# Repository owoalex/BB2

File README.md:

# BB2
Open source BLDC motor controller supporting >100A @ 20-60v

BB2 © 2023 is licensed under Attribution-ShareAlike 4.0 International. To view a copy of this license, visit http://creativecommons.org/licenses/by-sa/4.0/

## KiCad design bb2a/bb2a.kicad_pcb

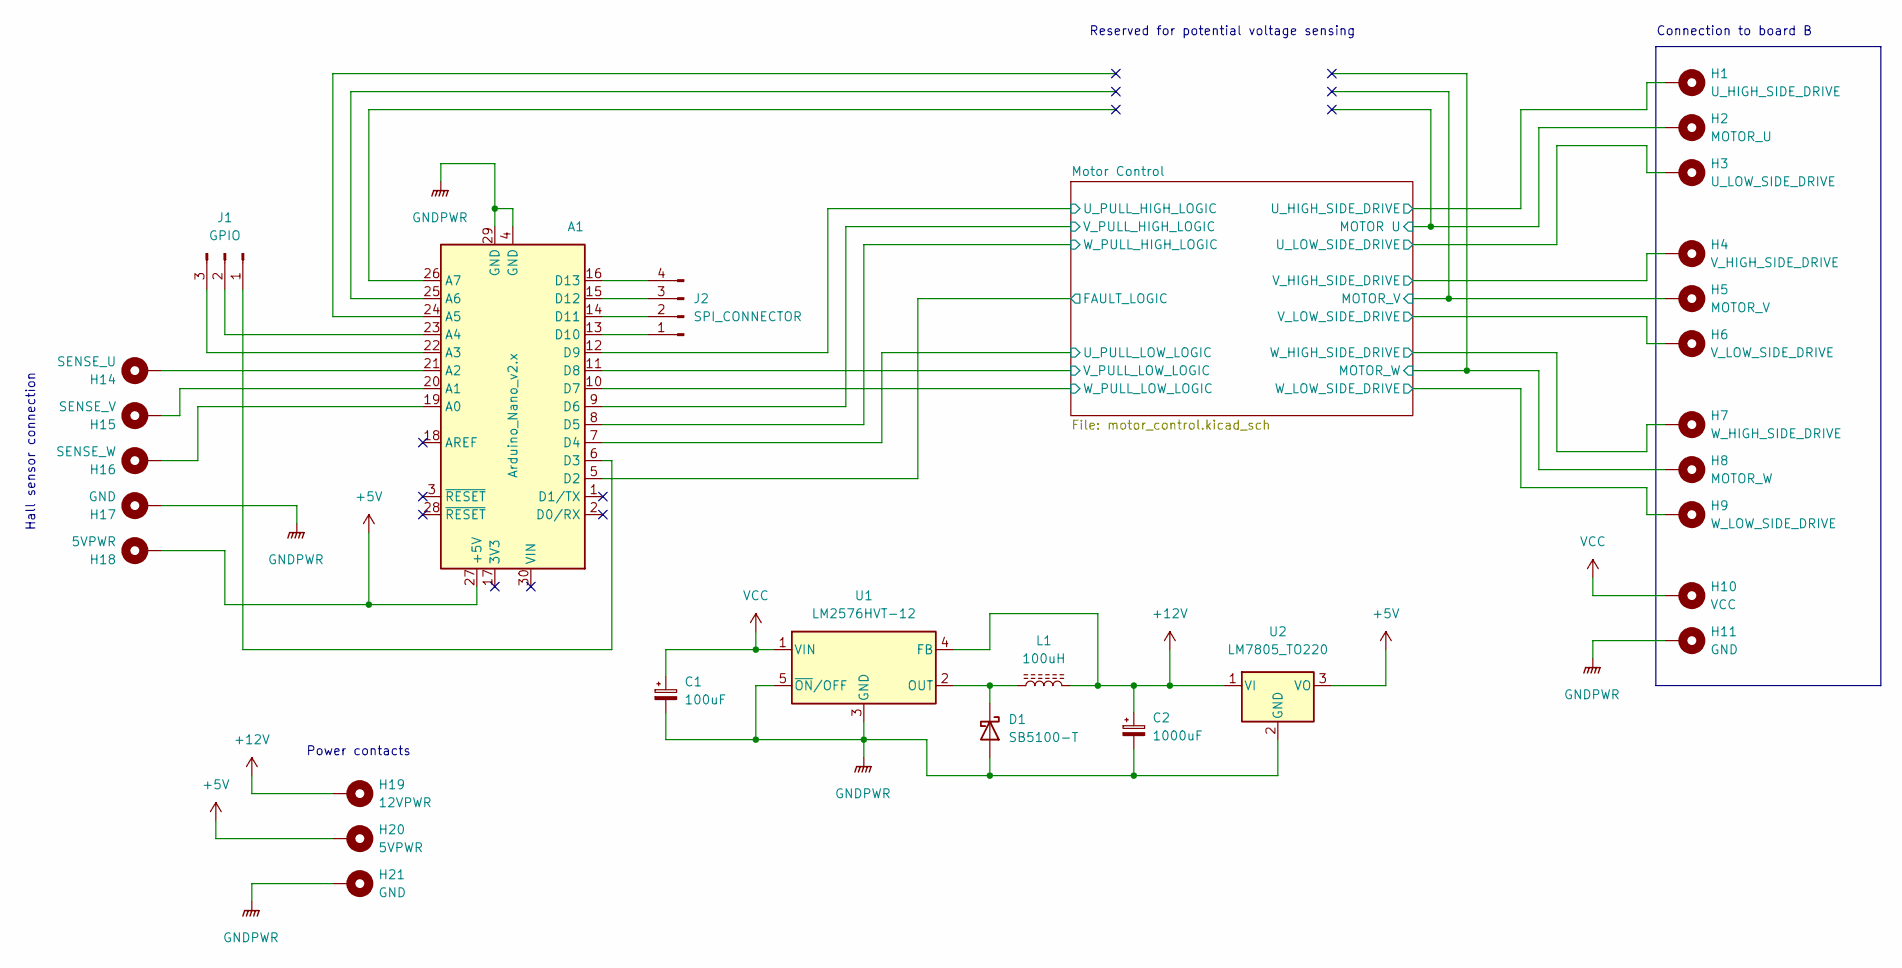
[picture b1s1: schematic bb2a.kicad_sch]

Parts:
A1: Arduino_Nano_v2.x; Arduino_Nano
C1: 100uF; CP_Radial_D6.3mm_P2.50mm
C2: 1000uF; CP_L18.0mm_D10.0mm_P5.00mm_Horizontal
D1: SB5100-T; D_DO-201AD_P15.24mm_Horizontal
H1: U_HIGH_SIDE_DRIVE; MountingHole_2.2mm_M2_Pad_Via
H2: MOTOR_U; MountingHole_2.2mm_M2_Pad_Via
H3: U_LOW_SIDE_DRIVE; MountingHole_2.2mm_M2_Pad_Via
H4: V_HIGH_SIDE_DRIVE; MountingHole_2.2mm_M2_Pad_Via
H5: MOTOR_V; MountingHole_2.2mm_M2_Pad_Via
H6: V_LOW_SIDE_DRIVE; MountingHole_2.2mm_M2_Pad_Via
H7: W_HIGH_SIDE_DRIVE; MountingHole_2.2mm_M2_Pad_Via
H8: MOTOR_W; MountingHole_2.2mm_M2_Pad_Via
H9: W_LOW_SIDE_DRIVE; MountingHole_2.2mm_M2_Pad_Via
H10: VCC; MountingHole_2.2mm_M2_Pad_Via
H11, H17, H21: GND; MountingHole_2.2mm_M2_Pad_Via
H14: SENSE_U; MountingHole_2.2mm_M2_Pad_Via
H15: SENSE_V; MountingHole_2.2mm_M2_Pad_Via
H16: SENSE_W; MountingHole_2.2mm_M2_Pad_Via
H18, H20: 5VPWR; MountingHole_2.2mm_M2_Pad_Via
H19: 12VPWR; MountingHole_2.2mm_M2_Pad_Via
J1: GPIO; PinHeader_1x03_P2.54mm_Vertical
J2: SPI_CONNECTOR; PinHeader_1x04_P2.54mm_Vertical
L1: 100uH; THT Toroidal Inductor Horizontal 25x12mm
U1: LM2576HVT-12; TO-220-5_P3.4x3.8mm_StaggerEven_Lead7.13mm_TabDown
U2: LM7805_TO220; TO-220-3_Horizontal_TabDown

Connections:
+5V: A1.27 (+5V), H18.1, H20.1, U2.3 (VO)
+12V: C2.1, H19.1, L1.2, U1.4 (FB), U2.1 (VI); also elsewhere on the board
/Motor Control/FAULT_LOGIC: A1.5 (D2); also elsewhere on the board
/Motor Control/MOTOR U: H2.1; also elsewhere on the board
/Motor Control/MOTOR_V: H5.1; also elsewhere on the board
/Motor Control/MOTOR_W: H8.1; also elsewhere on the board
/Motor Control/U_HIGH_SIDE_DRIVE: H1.1; also elsewhere on the board
/Motor Control/U_LOW_SIDE_DRIVE: H3.1; also elsewhere on the board
/Motor Control/U_PULL_HIGH_LOGIC: A1.12 (D9); also elsewhere on the board
/Motor Control/U_PULL_LOW_LOGIC: A1.7 (D4); also elsewhere on the board
/Motor Control/V_HIGH_SIDE_DRIVE: H4.1; also elsewhere on the board
/Motor Control/V_LOW_SIDE_DRIVE: H6.1; also elsewhere on the board
/Motor Control/V_PULL_HIGH_LOGIC: A1.9 (D6); also elsewhere on the board
/Motor Control/V_PULL_LOW_LOGIC: A1.11 (D8); also elsewhere on the board
/Motor Control/W_HIGH_SIDE_DRIVE: H7.1; also elsewhere on the board
/Motor Control/W_LOW_SIDE_DRIVE: H9.1; also elsewhere on the board
/Motor Control/W_PULL_HIGH_LOGIC: A1.8 (D5); also elsewhere on the board
/Motor Control/W_PULL_LOW_LOGIC: A1.10 (D7); also elsewhere on the board
GNDPWR: A1.4 (GND), A1.29 (GND), C1.2, C2.2, D1.2 (A), H11.1, H17.1, H21.1, U1.3 (GND), U1.5 (~ON/OFF), U2.2 (GND); also elsewhere on the board
unnamed: A1.13 (D10), J2.1
unnamed: A1.14 (D11), J2.2
unnamed: A1.15 (D12), J2.3
unnamed: A1.16 (D13), J2.4
unnamed: A1.19 (A0), H16.1
unnamed: A1.20 (A1), H15.1
unnamed: A1.21 (A2), H14.1
unnamed: A1.22 (A3), J1.3
unnamed: A1.23 (A4), J1.2
unnamed: D1.1 (K), L1.1, U1.2 (OUT)
unnamed: A1.6 (D3), J1.1
VCC: C1.1, H10.1, U1.1 (VIN)

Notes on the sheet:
Hall sensor connection
Reserved for potential voltage sensing
Power contacts
Connection to board B

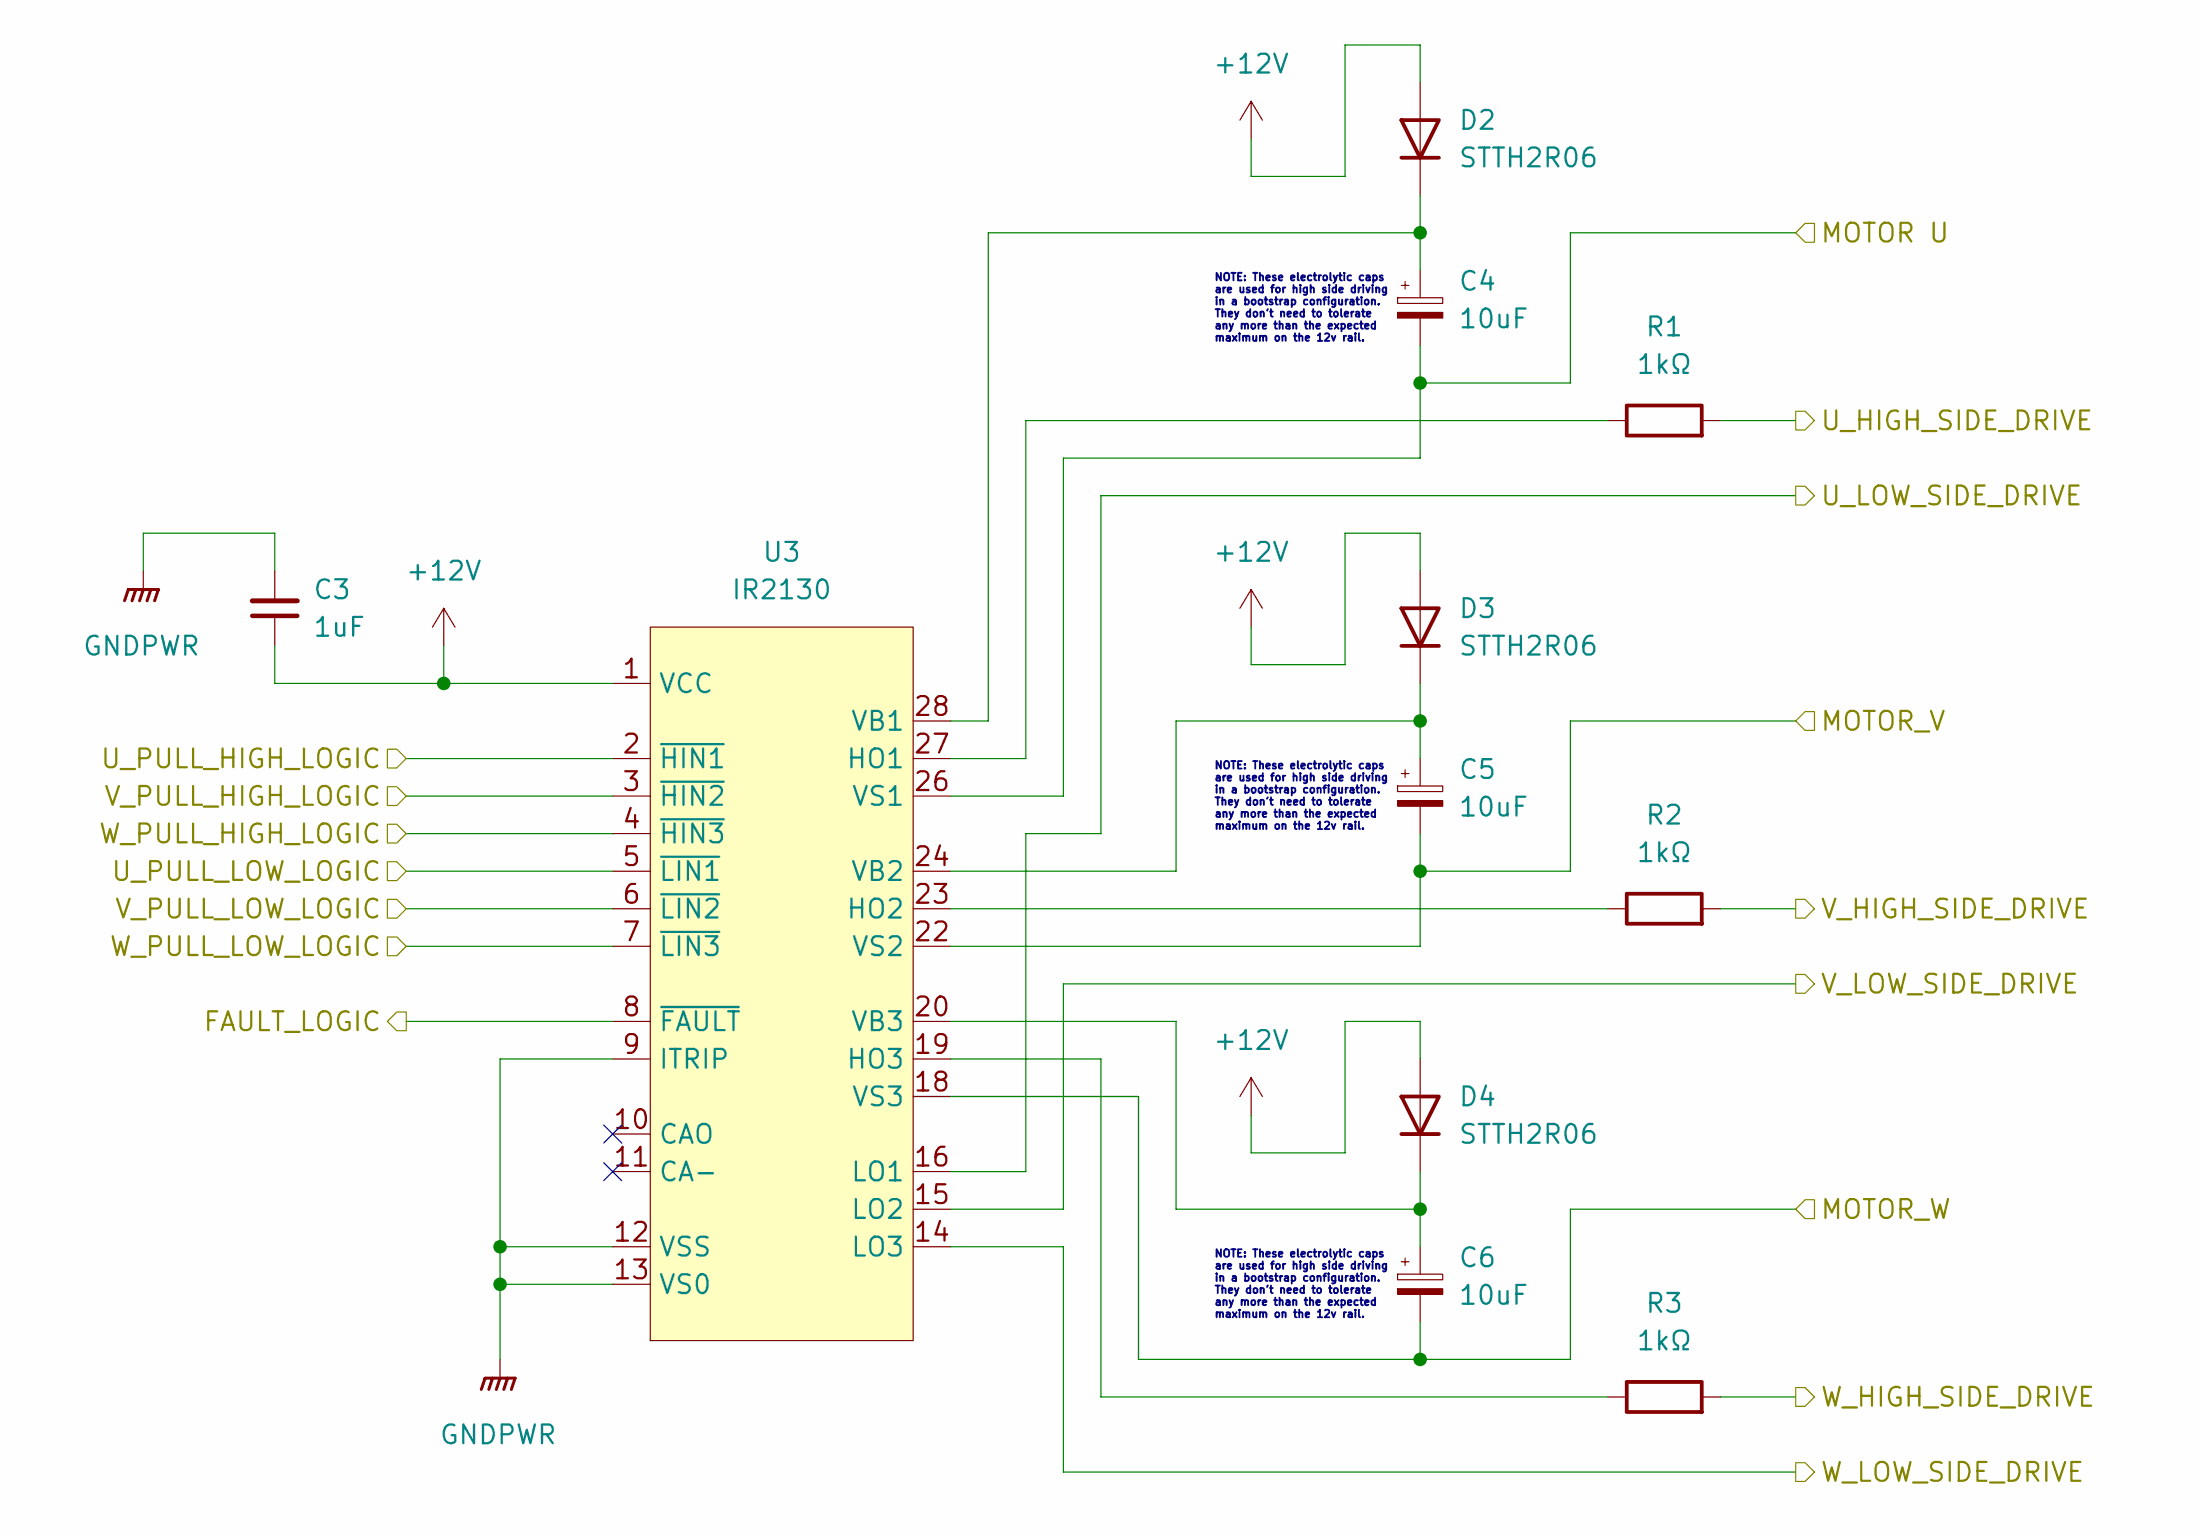
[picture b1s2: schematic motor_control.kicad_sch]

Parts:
C3: 1uF; C_Rect_L7.0mm_W2.0mm_P5.00mm
C4, C5, C6: 10uF; CP_Radial_D6.3mm_P2.50mm
D2, D3, D4: STTH2R06; D_T-1_P10.16mm_Horizontal
R1, R2, R3: 1kΩ; R_Axial_DIN0207_L6.3mm_D2.5mm_P10.16mm_Horizontal
U3: IR2130; DIP-28_W15.24mm

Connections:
+12V: C3.1, D2.2 (A), D3.2 (A), D4.2 (A), U3.1 (VCC); also elsewhere on the board
/Motor Control/FAULT_LOGIC: U3.8 (~FAULT); also elsewhere on the board
/Motor Control/MOTOR U: C4.2, U3.26 (VS1); also elsewhere on the board
/Motor Control/MOTOR_V: C5.2, U3.22 (VS2); also elsewhere on the board
/Motor Control/MOTOR_W: C6.2, U3.18 (VS3); also elsewhere on the board
/Motor Control/U_HIGH_SIDE_DRIVE: R1.2; also elsewhere on the board
/Motor Control/U_LOW_SIDE_DRIVE: U3.16 (LO1); also elsewhere on the board
/Motor Control/U_PULL_HIGH_LOGIC: U3.2 (~HIN1); also elsewhere on the board
/Motor Control/U_PULL_LOW_LOGIC: U3.5 (~LIN1); also elsewhere on the board
/Motor Control/V_HIGH_SIDE_DRIVE: R2.2; also elsewhere on the board
/Motor Control/V_LOW_SIDE_DRIVE: U3.15 (LO2); also elsewhere on the board
/Motor Control/V_PULL_HIGH_LOGIC: U3.3 (~HIN2); also elsewhere on the board
/Motor Control/V_PULL_LOW_LOGIC: U3.6 (~LIN2); also elsewhere on the board
/Motor Control/W_HIGH_SIDE_DRIVE: R3.2; also elsewhere on the board
/Motor Control/W_LOW_SIDE_DRIVE: U3.14 (LO3); also elsewhere on the board
/Motor Control/W_PULL_HIGH_LOGIC: U3.4 (~HIN3); also elsewhere on the board
/Motor Control/W_PULL_LOW_LOGIC: U3.7 (~LIN3); also elsewhere on the board
GNDPWR: C3.2, U3.9 (ITRIP), U3.12 (VSS), U3.13 (VS0); also elsewhere on the board
unnamed: C4.1, D2.1 (K), U3.28 (VB1)
unnamed: C5.1, D3.1 (K), U3.24 (VB2)
unnamed: C6.1, D4.1 (K), U3.20 (VB3)
unnamed: R1.1, U3.27 (HO1)
unnamed: R2.1, U3.23 (HO2)
unnamed: R3.1, U3.19 (HO3)

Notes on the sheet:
NOTE: These electrolytic caps are used for high side driving in a bootstrap configuration. They don't need to tolerate any more than the expected maximum on the 12v rail.

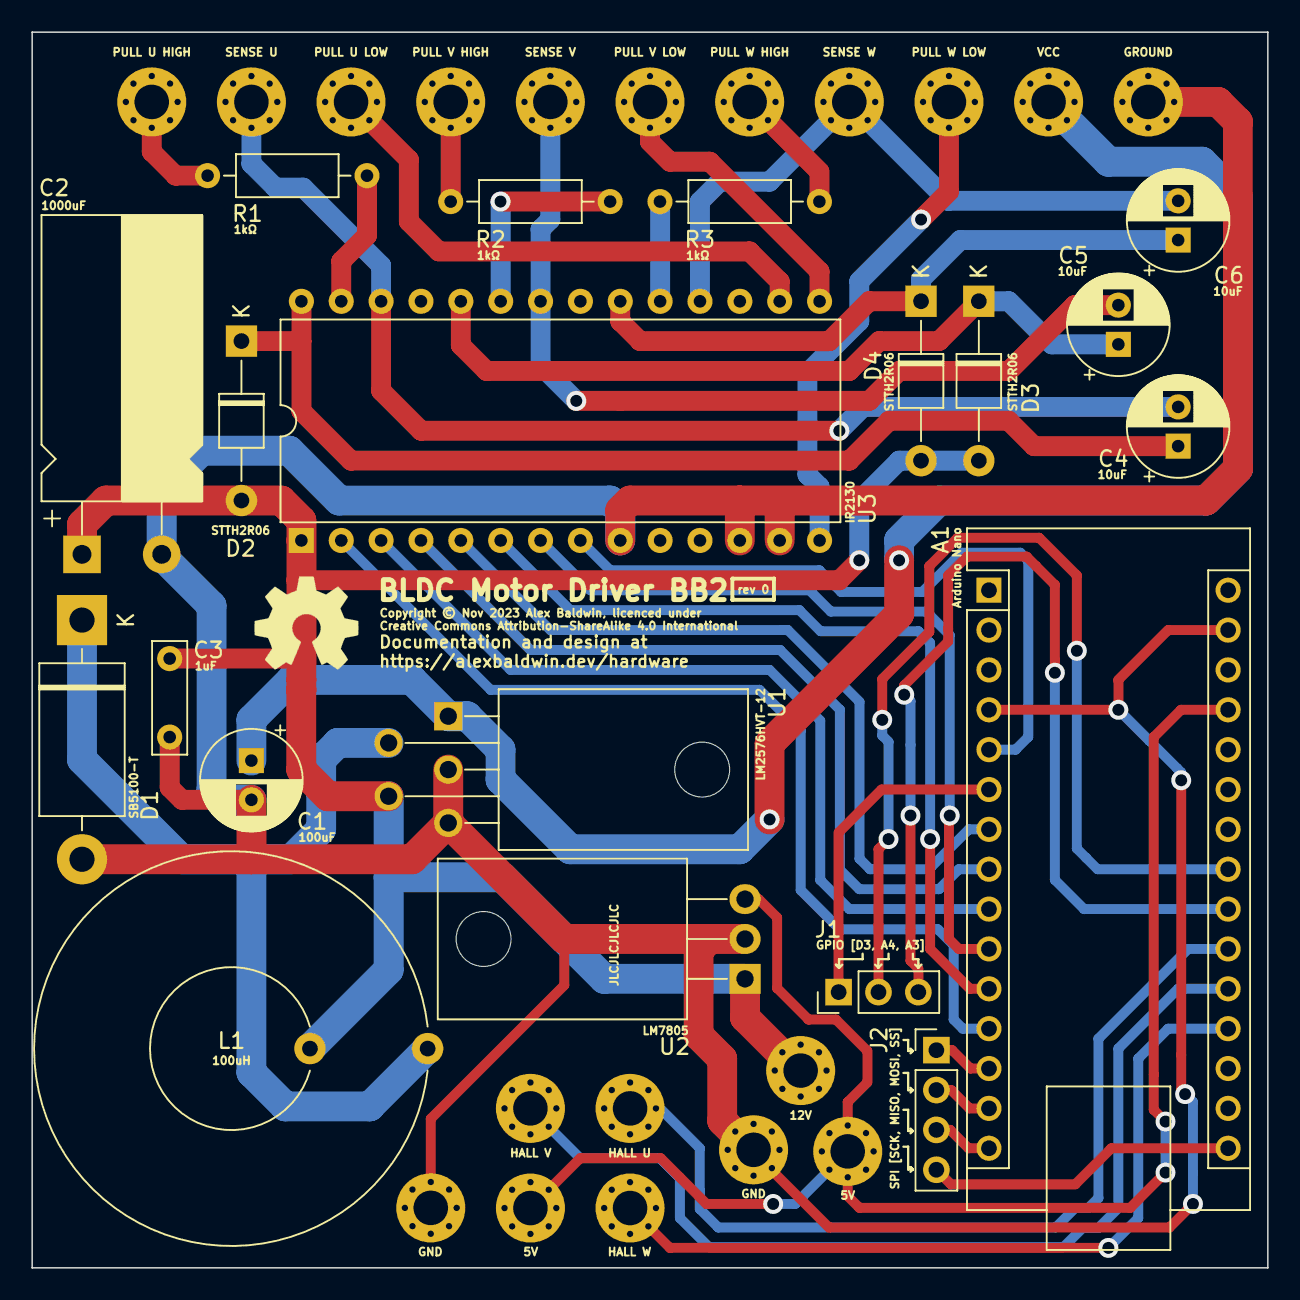
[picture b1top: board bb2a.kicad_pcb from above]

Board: 2 copper layers, 78.7 x 78.7 mm, 39 parts (0 on the bottom side), 37 nets.

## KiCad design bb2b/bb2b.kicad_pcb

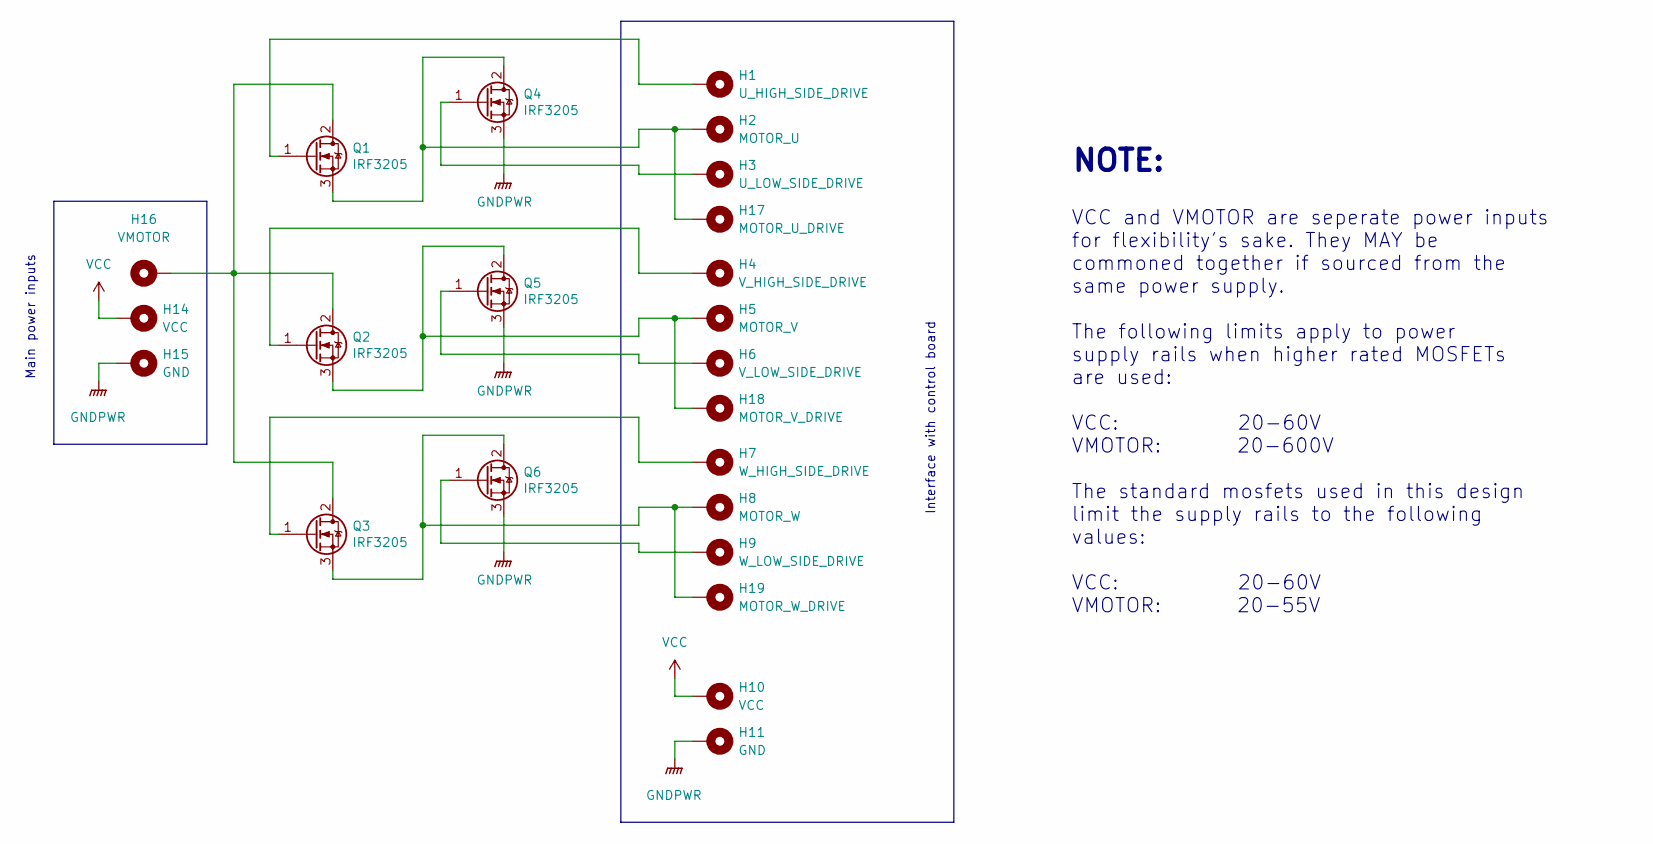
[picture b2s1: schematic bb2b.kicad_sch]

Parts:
H1: U_HIGH_SIDE_DRIVE; MountingHole_2.2mm_M2_Pad_Via
H2: MOTOR_U; MountingHole_2.2mm_M2_Pad_Via
H3: U_LOW_SIDE_DRIVE; MountingHole_2.2mm_M2_Pad_Via
H4: V_HIGH_SIDE_DRIVE; MountingHole_2.2mm_M2_Pad_Via
H5: MOTOR_V; MountingHole_2.2mm_M2_Pad_Via
H6: V_LOW_SIDE_DRIVE; MountingHole_2.2mm_M2_Pad_Via
H7: W_HIGH_SIDE_DRIVE; MountingHole_2.2mm_M2_Pad_Via
H8: MOTOR_W; MountingHole_2.2mm_M2_Pad_Via
H9: W_LOW_SIDE_DRIVE; MountingHole_2.2mm_M2_Pad_Via
H10: VCC; MountingHole_2.2mm_M2_Pad_Via
H11: GND; MountingHole_2.2mm_M2_Pad_Via
H14: VCC; MountingHole_4.3mm_M4_Pad_Via
H15: GND; MountingHole_4.3mm_M4_Pad_Via
H16: VMOTOR; MountingHole_4.3mm_M4_Pad_Via
H17: MOTOR_U_DRIVE; MountingHole_4.3mm_M4_Pad_Via
H18: MOTOR_V_DRIVE; MountingHole_4.3mm_M4_Pad_Via
H19: MOTOR_W_DRIVE; MountingHole_4.3mm_M4_Pad_Via
Q1, Q2, Q3, Q4, Q5, Q6: IRF3205; TO-220-3_Horizontal_TabUp

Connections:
GNDPWR: H11.1, H15.1, Q4.3 (S), Q5.3 (S), Q6.3 (S)
unnamed: H1.1, Q1.1 (G)
unnamed: H2.1, H17.1, Q1.3 (S), Q4.2 (D)
unnamed: H3.1, Q4.1 (G)
unnamed: H4.1, Q2.1 (G)
unnamed: H5.1, H18.1, Q2.3 (S), Q5.2 (D)
unnamed: H6.1, Q5.1 (G)
unnamed: H7.1, Q3.1 (G)
unnamed: H8.1, H19.1, Q3.3 (S), Q6.2 (D)
unnamed: H9.1, Q6.1 (G)
unnamed: H16.1, Q1.2 (D), Q2.2 (D), Q3.2 (D)
VCC: H10.1, H14.1

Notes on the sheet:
NOTE:
Main power inputs
VCC and VMOTOR are seperate power inputs for flexibility's sake. They MAY be commoned together if sourced from the same power supply. The following limits apply to power supply rails when higher rated MOSFETs are used: VCC: 20-60V VMOTOR: 20-600V The standard mosfets used in this design limit the s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
Interface with control board

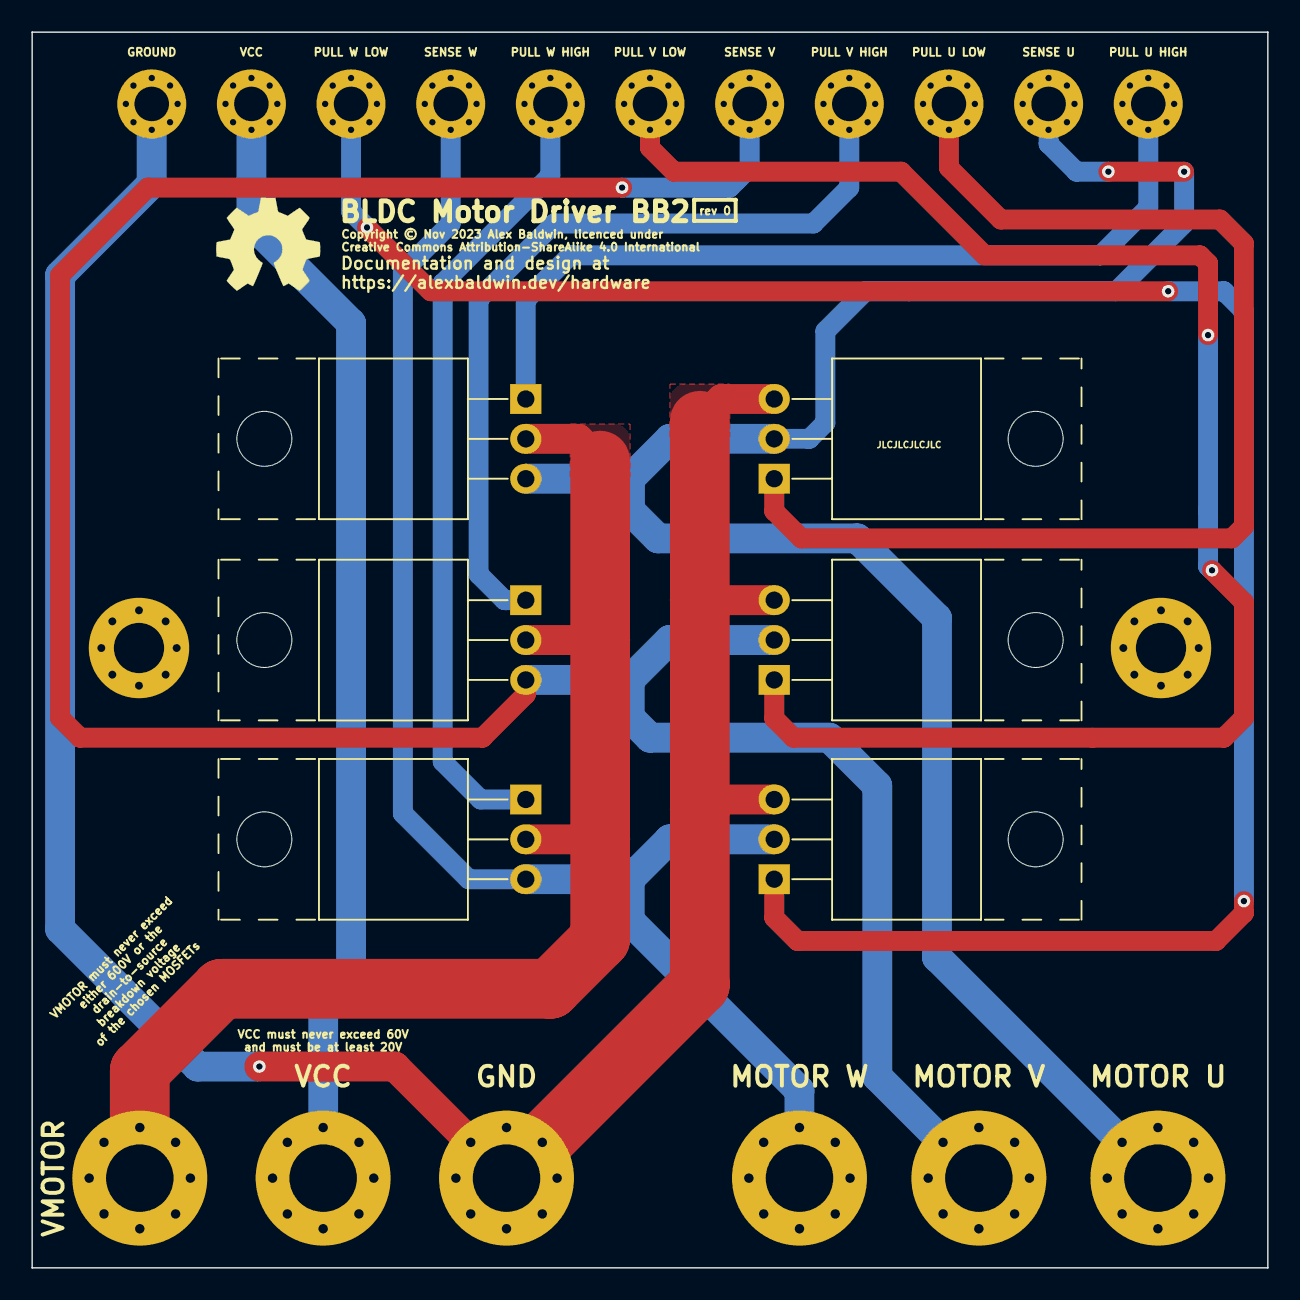
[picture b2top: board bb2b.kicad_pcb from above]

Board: 2 copper layers, 78.7 x 78.7 mm, 23 parts (0 on the bottom side), 12 nets.

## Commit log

2023-11-06 Initial work
2023-11-06 Adding licence

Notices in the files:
bb2a/bb2a.kicad_pcb:
Copyright © Nov 2023 Alex Baldwin, licenced under
Creative Commons Attribution-ShareAlike 4.0 International
